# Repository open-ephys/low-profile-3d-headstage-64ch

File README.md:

# low-profile-3d-headstage-64ch
Design files of the low profile spi headstage with 64ch channels and 3D orientation.

## Licensing

The designs, documentation, and photos available in this repository are free: you can redistribute it and/or modify it under the terms of the used license.
Check file named LICENSE.

<br />This work is licensed under a <a rel="license" href="http://creativecommons.org/licenses/by-nc-sa/3.0/igo/">Creative Commons Attribution-NonCommercial-ShareAlike 3.0 IGO License</a>.

[1]: https://docs.google.com/spreadsheets/d/1aobmmEzBDethzIlrm1eg0eYkBqlyX3s9WbA9KgRwVQI/edit?usp=sharing

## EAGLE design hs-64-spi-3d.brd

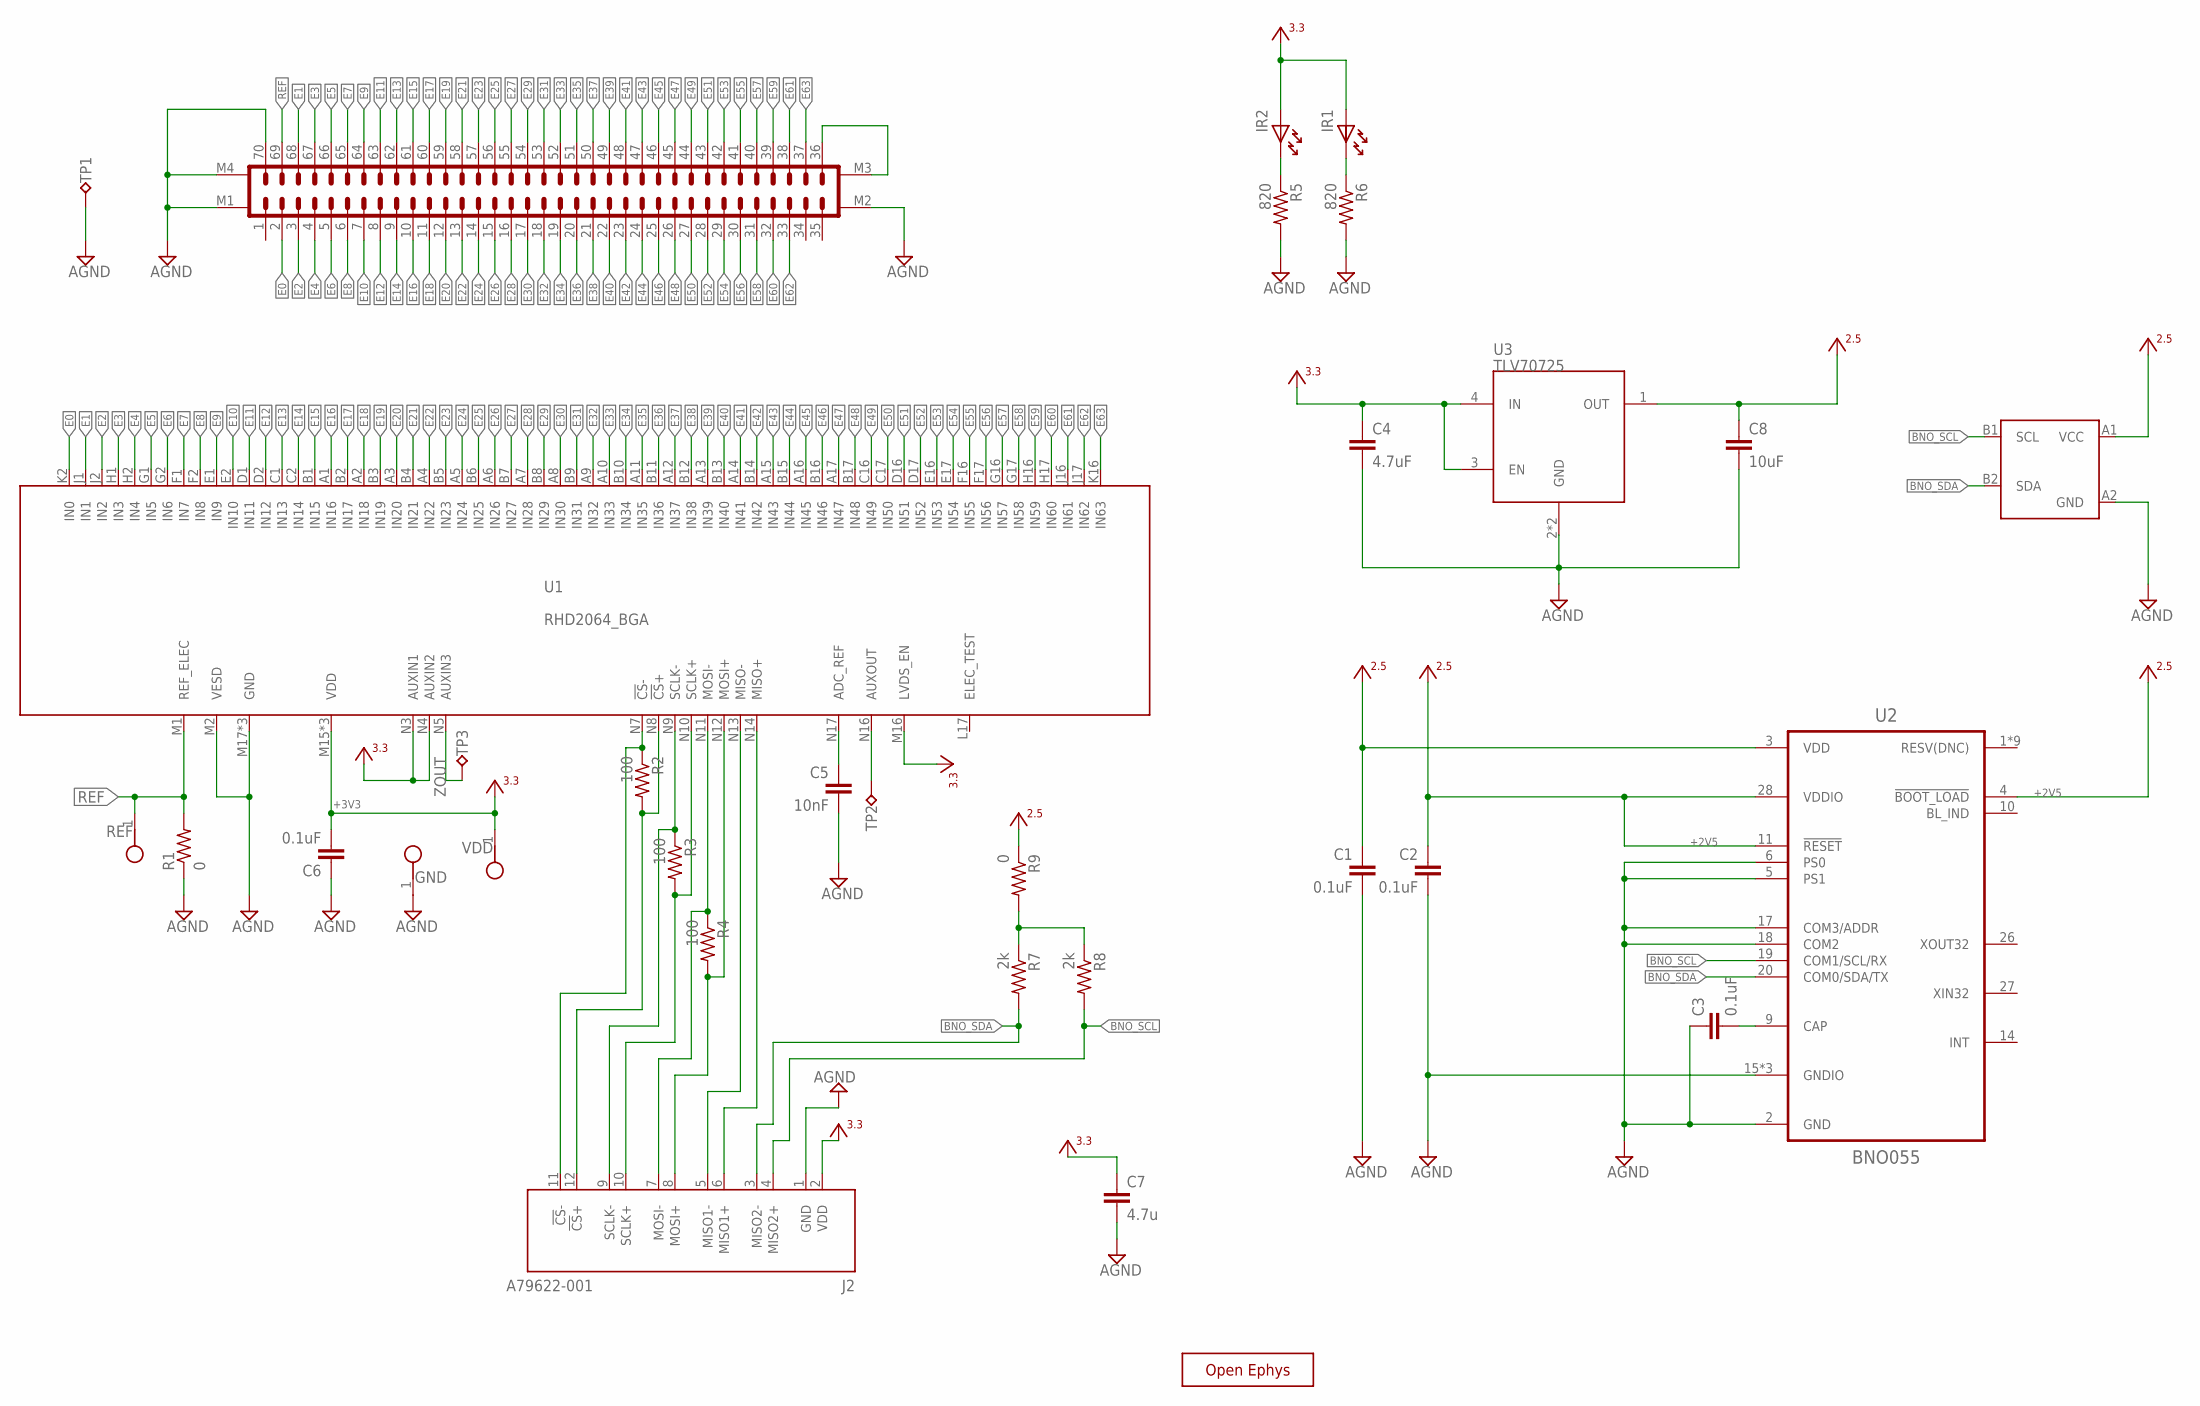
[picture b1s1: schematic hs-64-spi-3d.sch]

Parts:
C1, C2, C6: 0.1uF; 0402T
C3: 0.1uF; 0201T
C4: 4.7uF; 0402T; PARTNO CL05A105KO5NNNC
C5: 10nF; 0402T; PARTNO GRM033R71E103KE14D
C7: 4.7u; 0402
C8: 10uF; 0402T; PARTNO CL05A106MQ5NUNC
GND: TESTPOINT_SMALL
IR1, IR2: LEDHAND; LED_HAND
J1: DF40C-70DP-0.4V(51); DF40-70HEAD-LESS-SILK
J2: A79622-001
R1: 0; 0603
R2, R3, R4: 100; 0402
R5, R6: 820; 0402
R7, R8: 2k; 0201T
R9: 0; 0201T
REF: TESTPOINT_SMALL
TP1, TP2, TP3: VCC; TP07R
U1: RHD2064_BGA; BGA104_0.5MM
U2: BNO055; LGA-28-3.8X5.2
U3: TLV70725; X2SON
U4: 24CW640T-I/CS0668; 4-BALL_WAFFER_0.4MMX0.4MM
VDD: TESTPOINT_SMALL
X: OE-LOGO_3.5X2.5; OE-LOGO-3.5X2.5

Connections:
+2V5: C1.1, C2.1, C8.1, R9.1, U2.3 (VDD), U2.4 (!BOOT_LOAD), U2.11 (!RESET), U2.28 (VDDIO), U3.1 (OUT), U4.A1 (VCC)
+3V3: C4.1, C6.2, C7.1, IR1.A, IR2.A, J2.2 (VDD), U1.M15 (VDD), U1.M16 (LVDS_EN), U1.N2 (VDD), U1.N3 (AUXIN1), U1.N4 (AUXIN2), U1.N15 (VDD), U3.3 (EN), U3.4 (IN), VDD.1
AGND: C1.2, C2.2, C3.1, C4.2, C5.2, C6.1, C7.2, C8.2, GND.1, J1.70, J1.M1, J1.M2, J1.M4, J2.1 (GND), R1.1, R5.2, R6.2, TP1.TP, U1.M2 (VESD), U1.M17 (GND), U1.N1 (GND), U1.N6 (GND), U2.2 (GND), U2.5 (PS1), U2.6 (PS0), U2.15 (GNDIO), U2.16 (GNDIO), U2.17 (COM3/ADDR), U2.18 (COM2), U2.25 (GNDIO), U3.2 (GND), U3.PAD (GND), U4.A2 (GND)
BNO_SCL: J2.4 (MISO2+), R8.2, U2.19 (COM1/SCL/RX), U4.B1 (SCL)
BNO_SDA: J2.3 (MISO2-), R7.2, U2.20 (COM0/SDA/TX), U4.B2 (SDA)
E0: J1.2, U1.K2 (IN0)
E1: J1.68, U1.J1 (IN1)
E2: J1.3, U1.J2 (IN2)
E3: J1.67, U1.H1 (IN3)
E4: J1.4, U1.H2 (IN4)
E5: J1.66, U1.G1 (IN5)
E6: J1.5, U1.G2 (IN6)
E7: J1.65, U1.F1 (IN7)
E8: J1.6, U1.F2 (IN8)
E9: J1.64, U1.E1 (IN9)
E10: J1.7, U1.E2 (IN10)
E11: J1.63, U1.D1 (IN11)
E12: J1.8, U1.D2 (IN12)
E13: J1.62, U1.C1 (IN13)
E14: J1.9, U1.C2 (IN14)
E15: J1.61, U1.B1 (IN15)
E16: J1.10, U1.A1 (IN16)
E17: J1.60, U1.B2 (IN17)
E18: J1.11, U1.A2 (IN18)
E19: J1.59, U1.B3 (IN19)
E20: J1.12, U1.A3 (IN20)
E21: J1.58, U1.B4 (IN21)
E22: J1.13, U1.A4 (IN22)
E23: J1.57, U1.B5 (IN23)
E24: J1.14, U1.A5 (IN24)
E25: J1.56, U1.B6 (IN25)
E26: J1.15, U1.A6 (IN26)
E27: J1.55, U1.B7 (IN27)
E28: J1.16, U1.A7 (IN28)
E29: J1.54, U1.B8 (IN29)
E30: J1.17, U1.A8 (IN30)
E31: J1.53, U1.B9 (IN31)
E32: J1.18, U1.A9 (IN32)
E33: J1.52, U1.A10 (IN33)
E34: J1.19, U1.B10 (IN34)
E35: J1.51, U1.A11 (IN35)
E36: J1.20, U1.B11 (IN36)
E37: J1.50, U1.A12 (IN37)
E38: J1.21, U1.B12 (IN38)
E39: J1.49, U1.A13 (IN39)
E40: J1.22, U1.B13 (IN40)
E41: J1.48, U1.A14 (IN41)
E42: J1.23, U1.B14 (IN42)
E43: J1.47, U1.A15 (IN43)
E44: J1.24, U1.B15 (IN44)
E45: J1.46, U1.A16 (IN45)
E46: J1.25, U1.B16 (IN46)
E47: J1.45, U1.A17 (IN47)
E48: J1.26, U1.B17 (IN48)
E49: J1.44, U1.C16 (IN49)
E50: J1.27, U1.C17 (IN50)
E51: J1.43, U1.D16 (IN51)
E52: J1.28, U1.D17 (IN52)
E53: J1.42, U1.E16 (IN53)
E54: J1.29, U1.E17 (IN54)
E55: J1.41, U1.F16 (IN55)
E56: J1.30, U1.F17 (IN56)
E57: J1.40, U1.G16 (IN57)
E58: J1.31, U1.G17 (IN58)
E59: J1.39, U1.H16 (IN59)
E60: J1.32, U1.H17 (IN60)
E61: J1.38, U1.J16 (IN61)
E62: J1.33, U1.J17 (IN62)
E63: J1.37, U1.K16 (IN63)
unnamed: R7.1, R8.1, R9.2
unnamed: IR2.K, R5.1
unnamed: IR1.K, R6.1
unnamed: C5.1, U1.N17 (ADC_REF)
unnamed: TP2.TP, U1.N16 (AUXOUT)
unnamed: C3.2, U2.9 (CAP)
REF: J1.69, R1.2, REF.1, U1.M1 (REF_ELEC)
RHD_CLK_N: J2.9 (SCLK-), R3.1, U1.N9 (SCLK-)
RHD_CLK_P: J2.10 (SCLK+), R3.2, U1.N10 (SCLK+)
RHD_CS_N: J2.11 (!CS!-), R2.1, U1.N7 (!CS!-)
RHD_CS_P: J2.12 (!CS!+), R2.2, U1.N8 (!CS!+)
RHD_MISO_N: J2.5 (MISO1-), U1.N13 (MISO-)
RHD_MISO_P: J2.6 (MISO1+), U1.N14 (MISO+)
RHD_MOSI_N: J2.7 (MOSI-), R4.1, U1.N11 (MOSI-)
RHD_MOSI_P: J2.8 (MOSI+), R4.2, U1.N12 (MOSI+)
VCOAX: J1.36, J1.M3
ZOUT: TP3.TP, U1.N5 (AUXIN3)

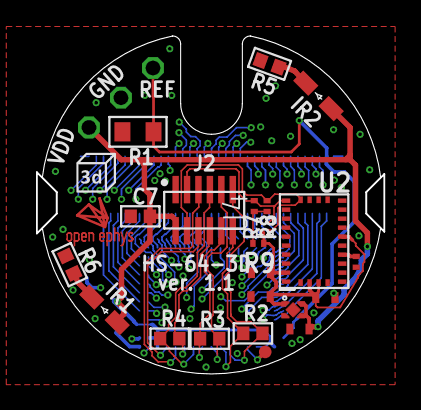
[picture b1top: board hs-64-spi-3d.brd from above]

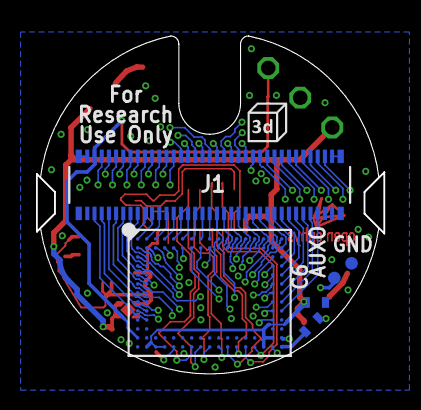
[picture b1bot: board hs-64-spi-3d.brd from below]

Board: 4 copper layers, 19.3 x 18.7 mm, 32 parts (6 on the bottom side), 86 nets.

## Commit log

2023-09-10 Added PCB design files.
2023-09-10 Added mechanical dimensions.
2023-09-10 Renamed file.
2023-09-10 Decreased I2C pull-up resistors to 2k.
2023-09-10 Connection between REF to GND is now done by default.
2023-09-10 Added production files.
2023-10-07 Corrected C4 and C7 values to 4.7uF.
2024-03-20 Updated Hirose (J1) schematic.
2024-10-17 Added 3d logo.
2024-10-17 Updated gerber files.
2024-10-17 Added license.
2025-02-13 Added .gitignore.
2025-02-13 Add mouse bites restrictions.
2025-02-18 Added EEPROM.

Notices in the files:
hs-64-spi-3d.sch:
LICENSE: CERN OHL v1.2
